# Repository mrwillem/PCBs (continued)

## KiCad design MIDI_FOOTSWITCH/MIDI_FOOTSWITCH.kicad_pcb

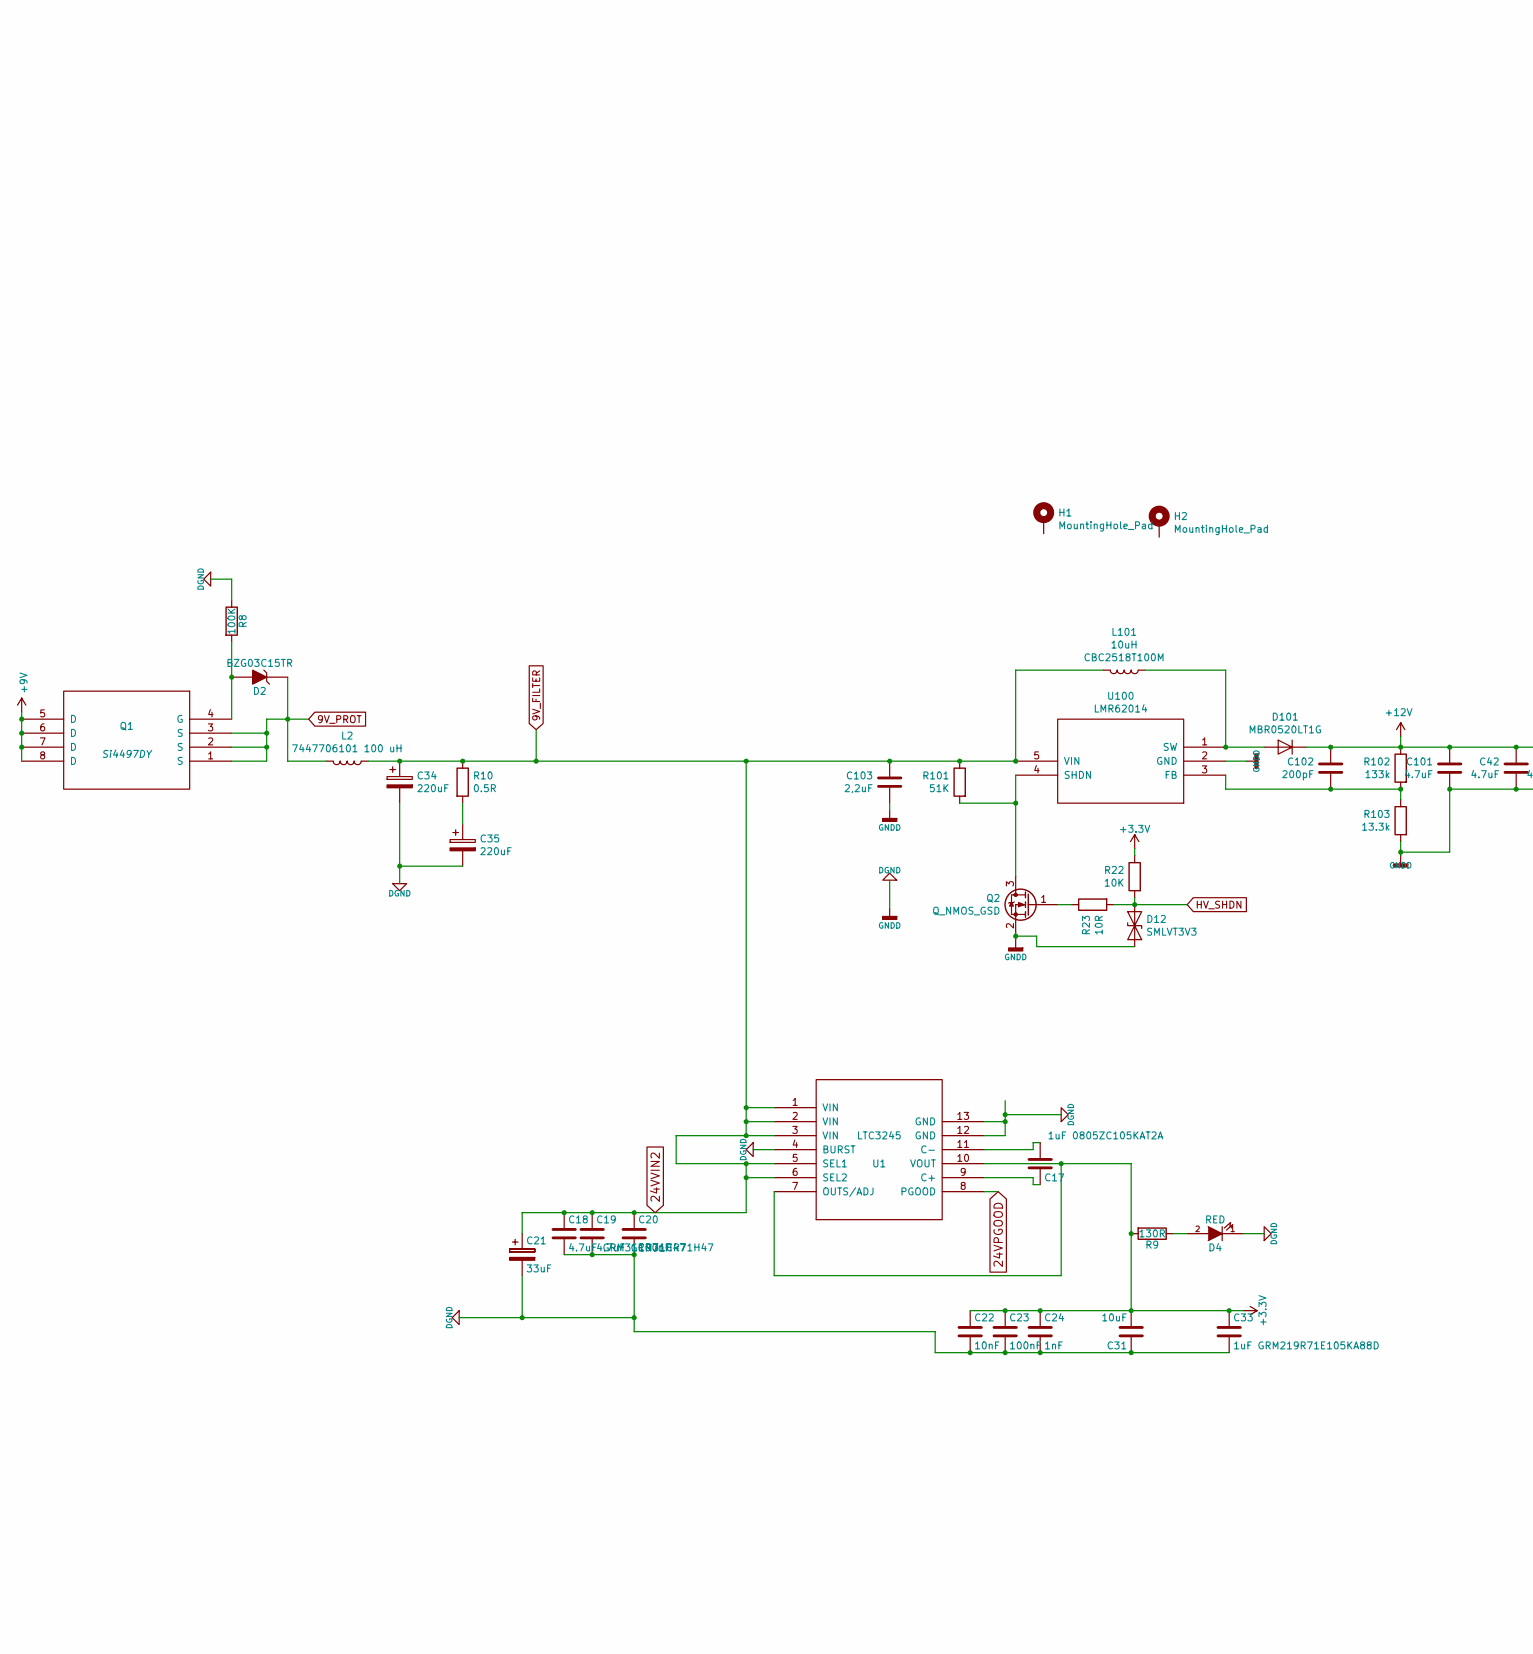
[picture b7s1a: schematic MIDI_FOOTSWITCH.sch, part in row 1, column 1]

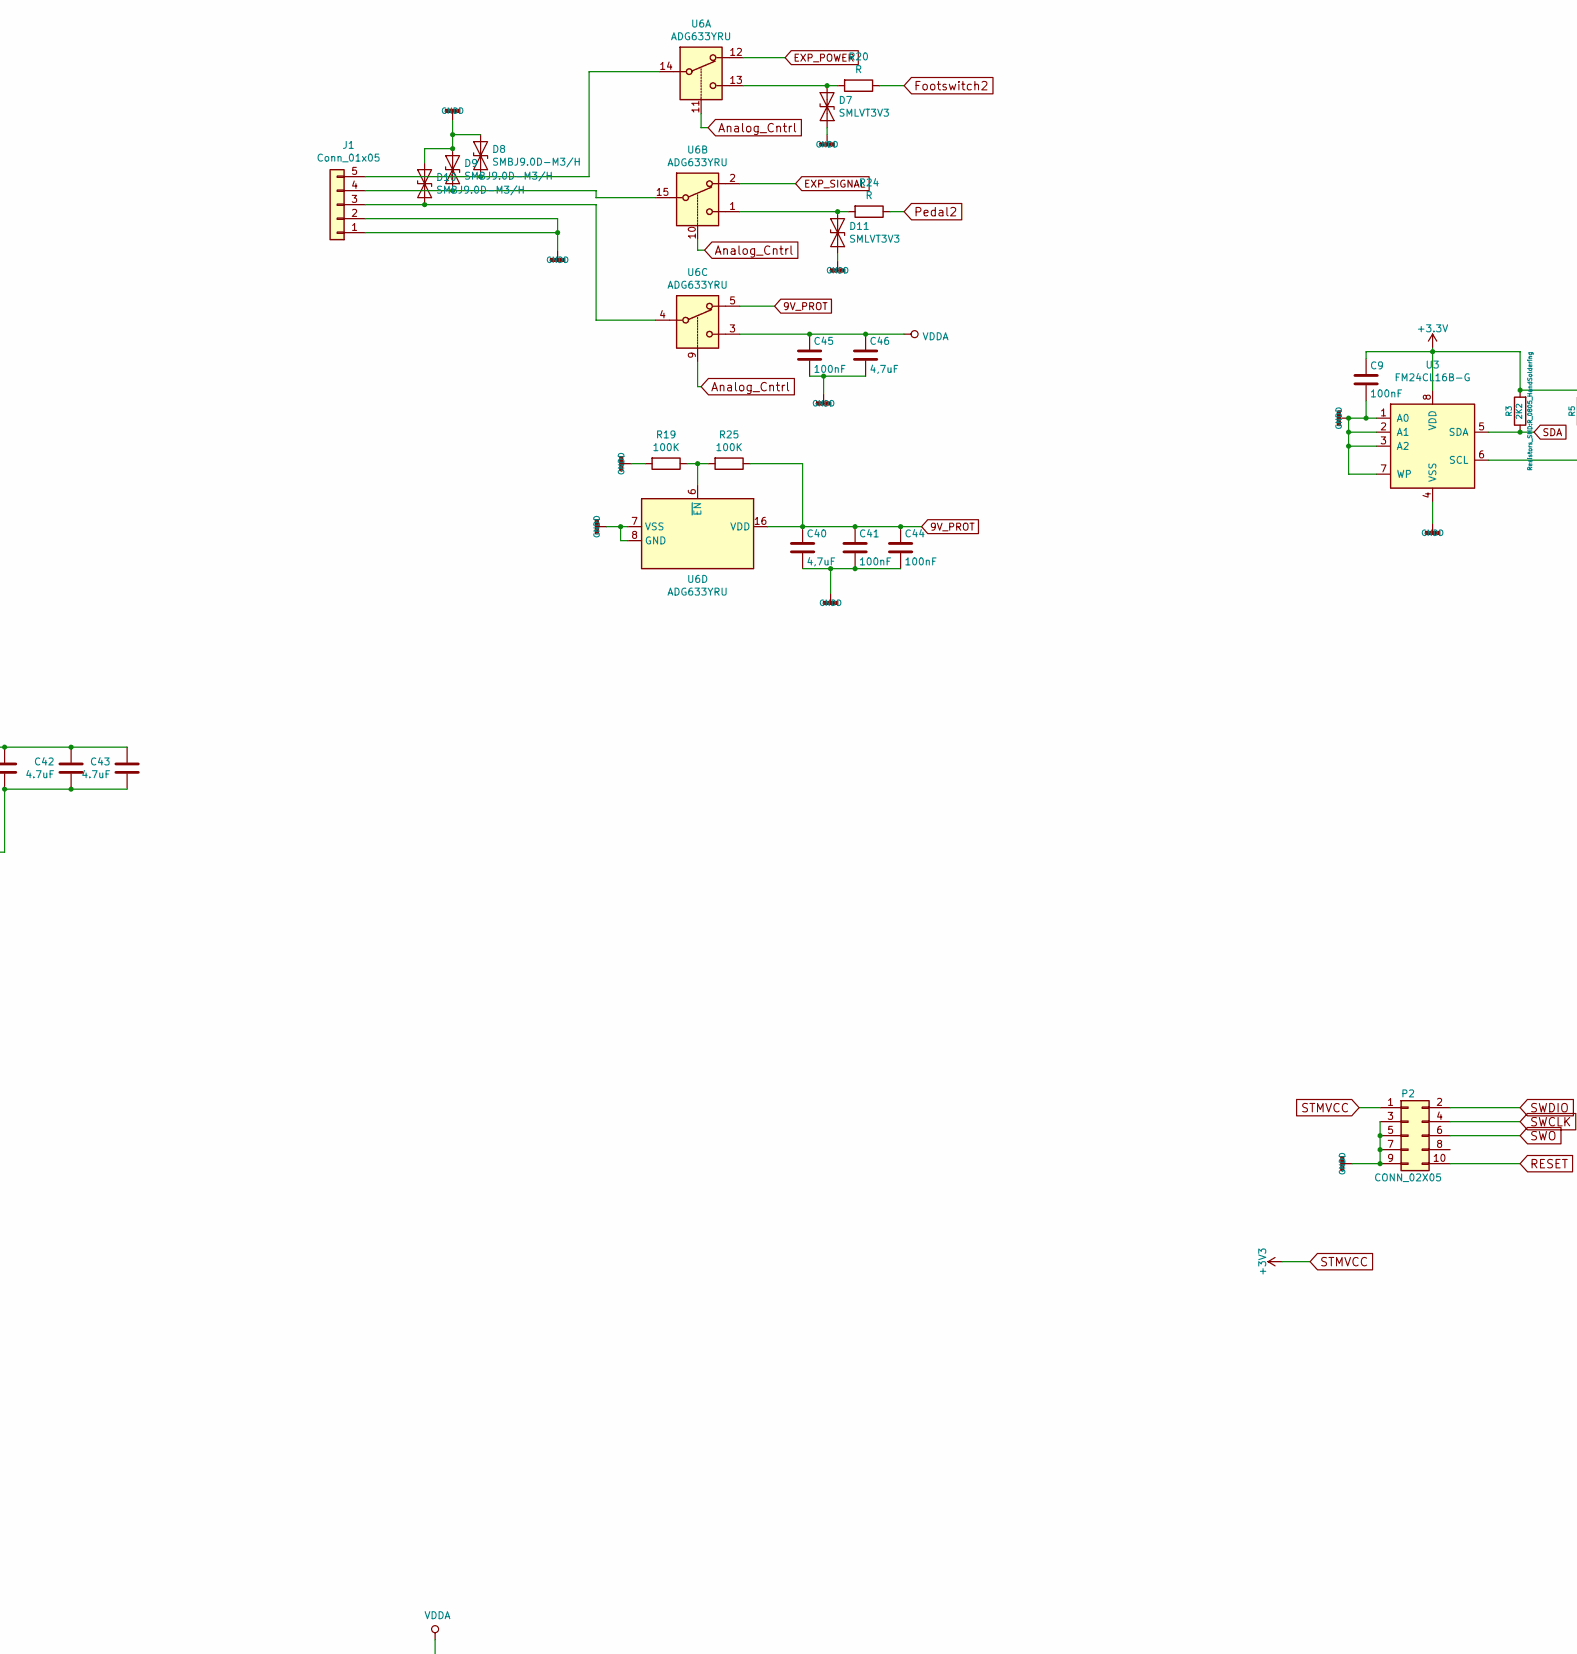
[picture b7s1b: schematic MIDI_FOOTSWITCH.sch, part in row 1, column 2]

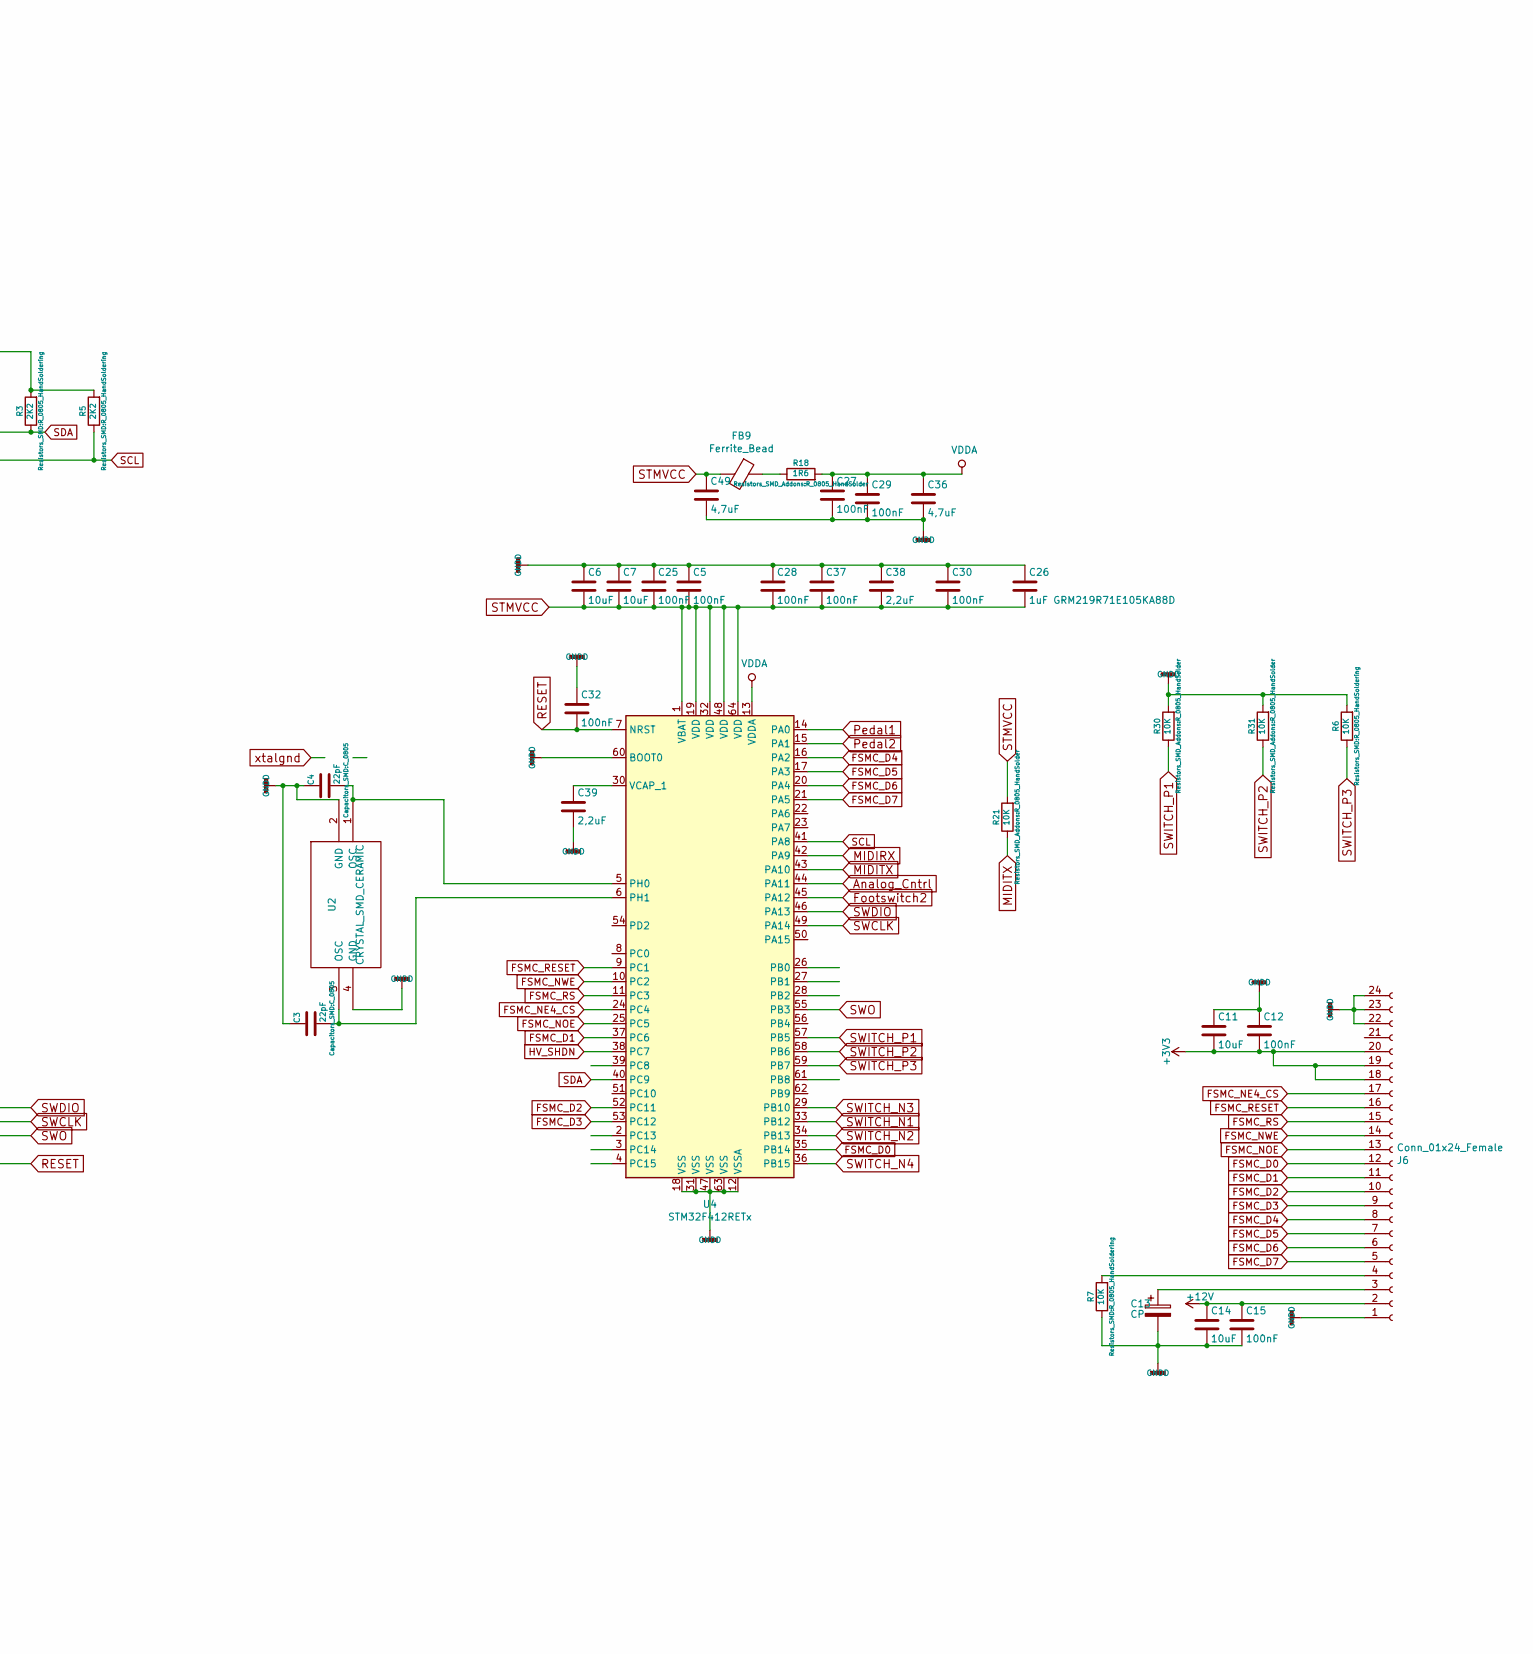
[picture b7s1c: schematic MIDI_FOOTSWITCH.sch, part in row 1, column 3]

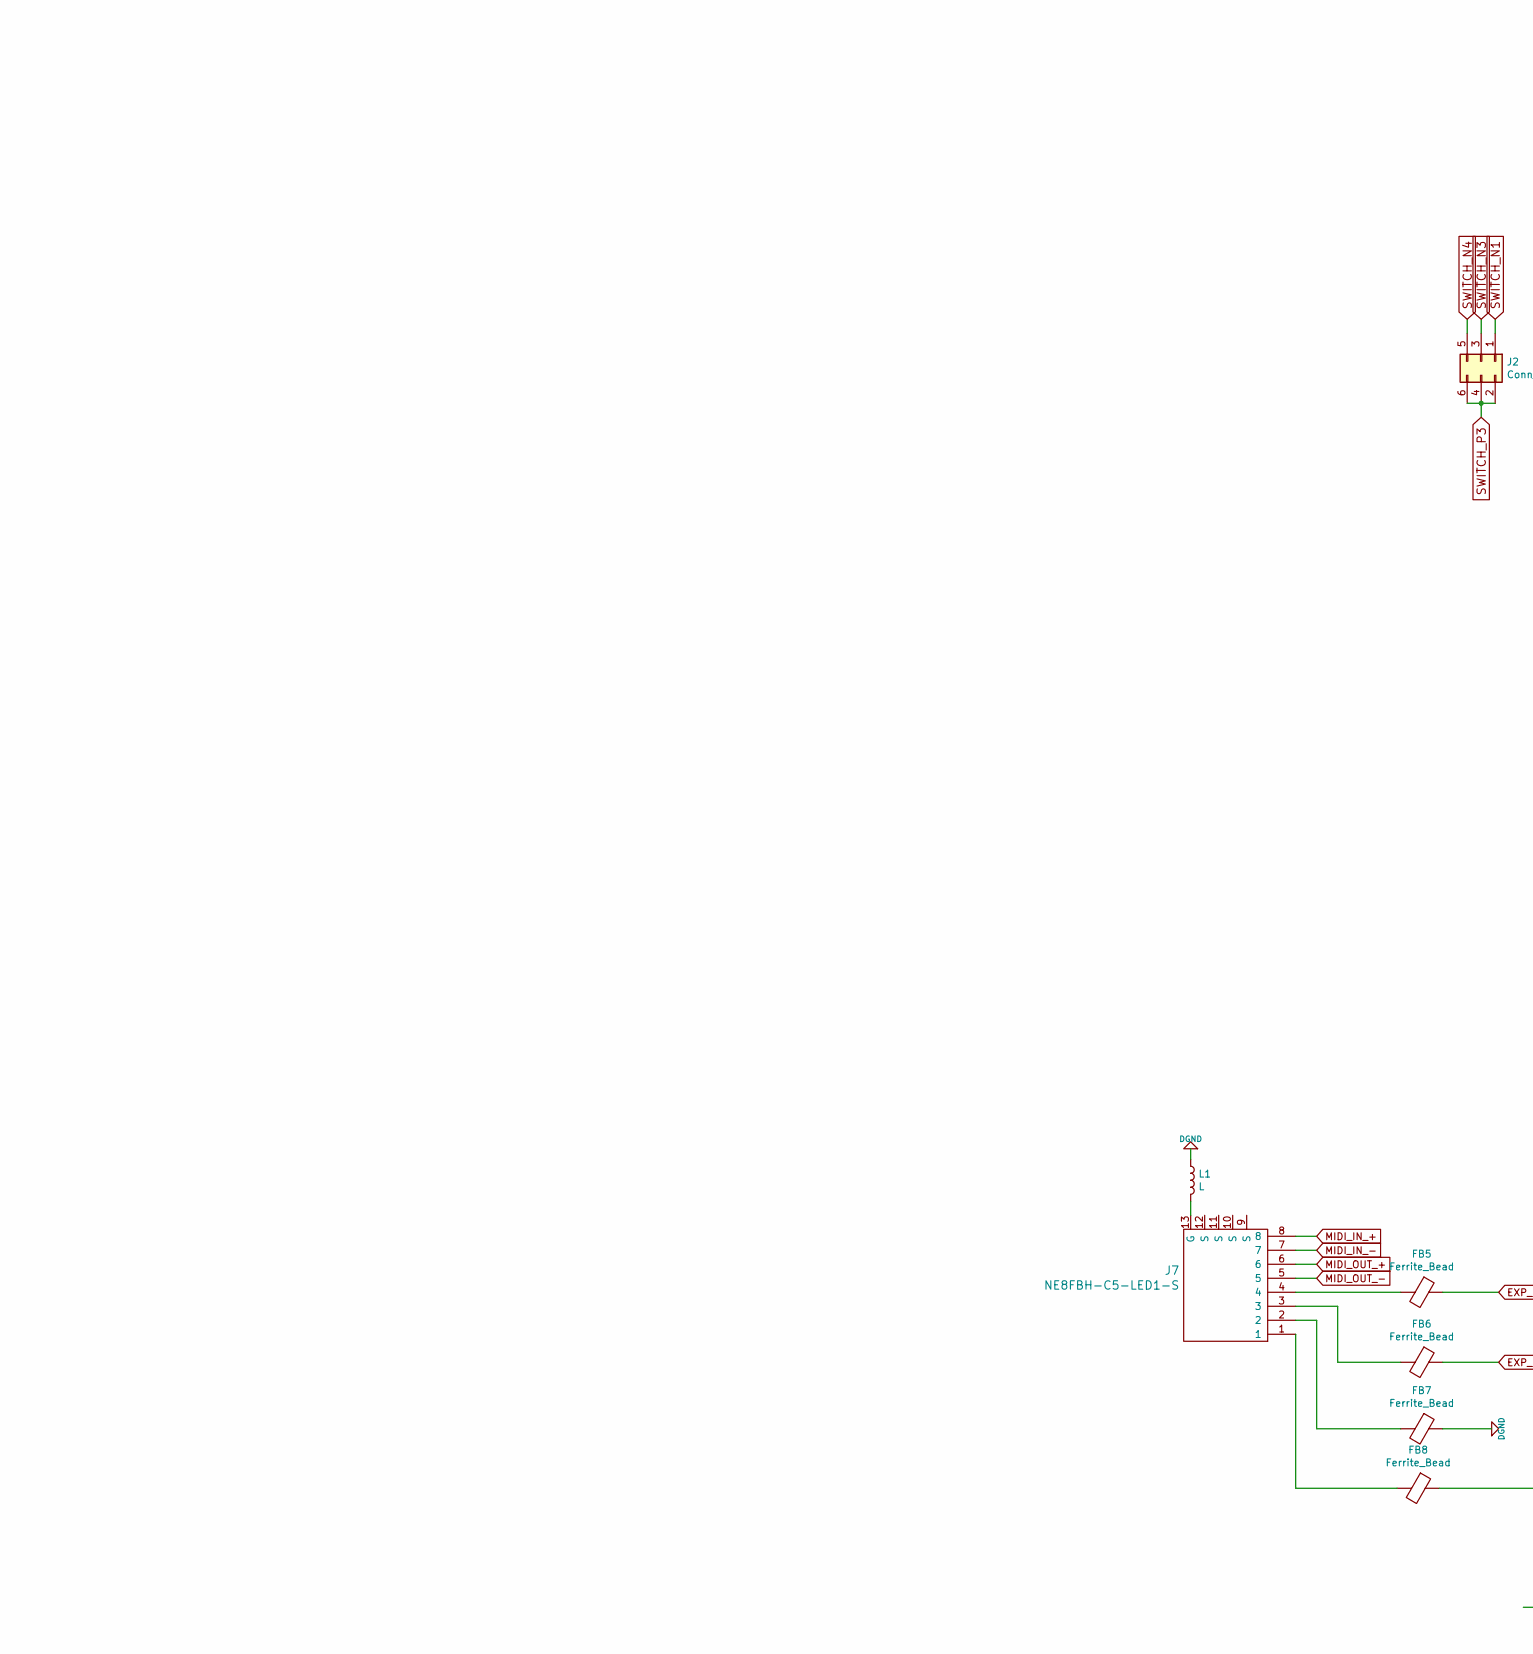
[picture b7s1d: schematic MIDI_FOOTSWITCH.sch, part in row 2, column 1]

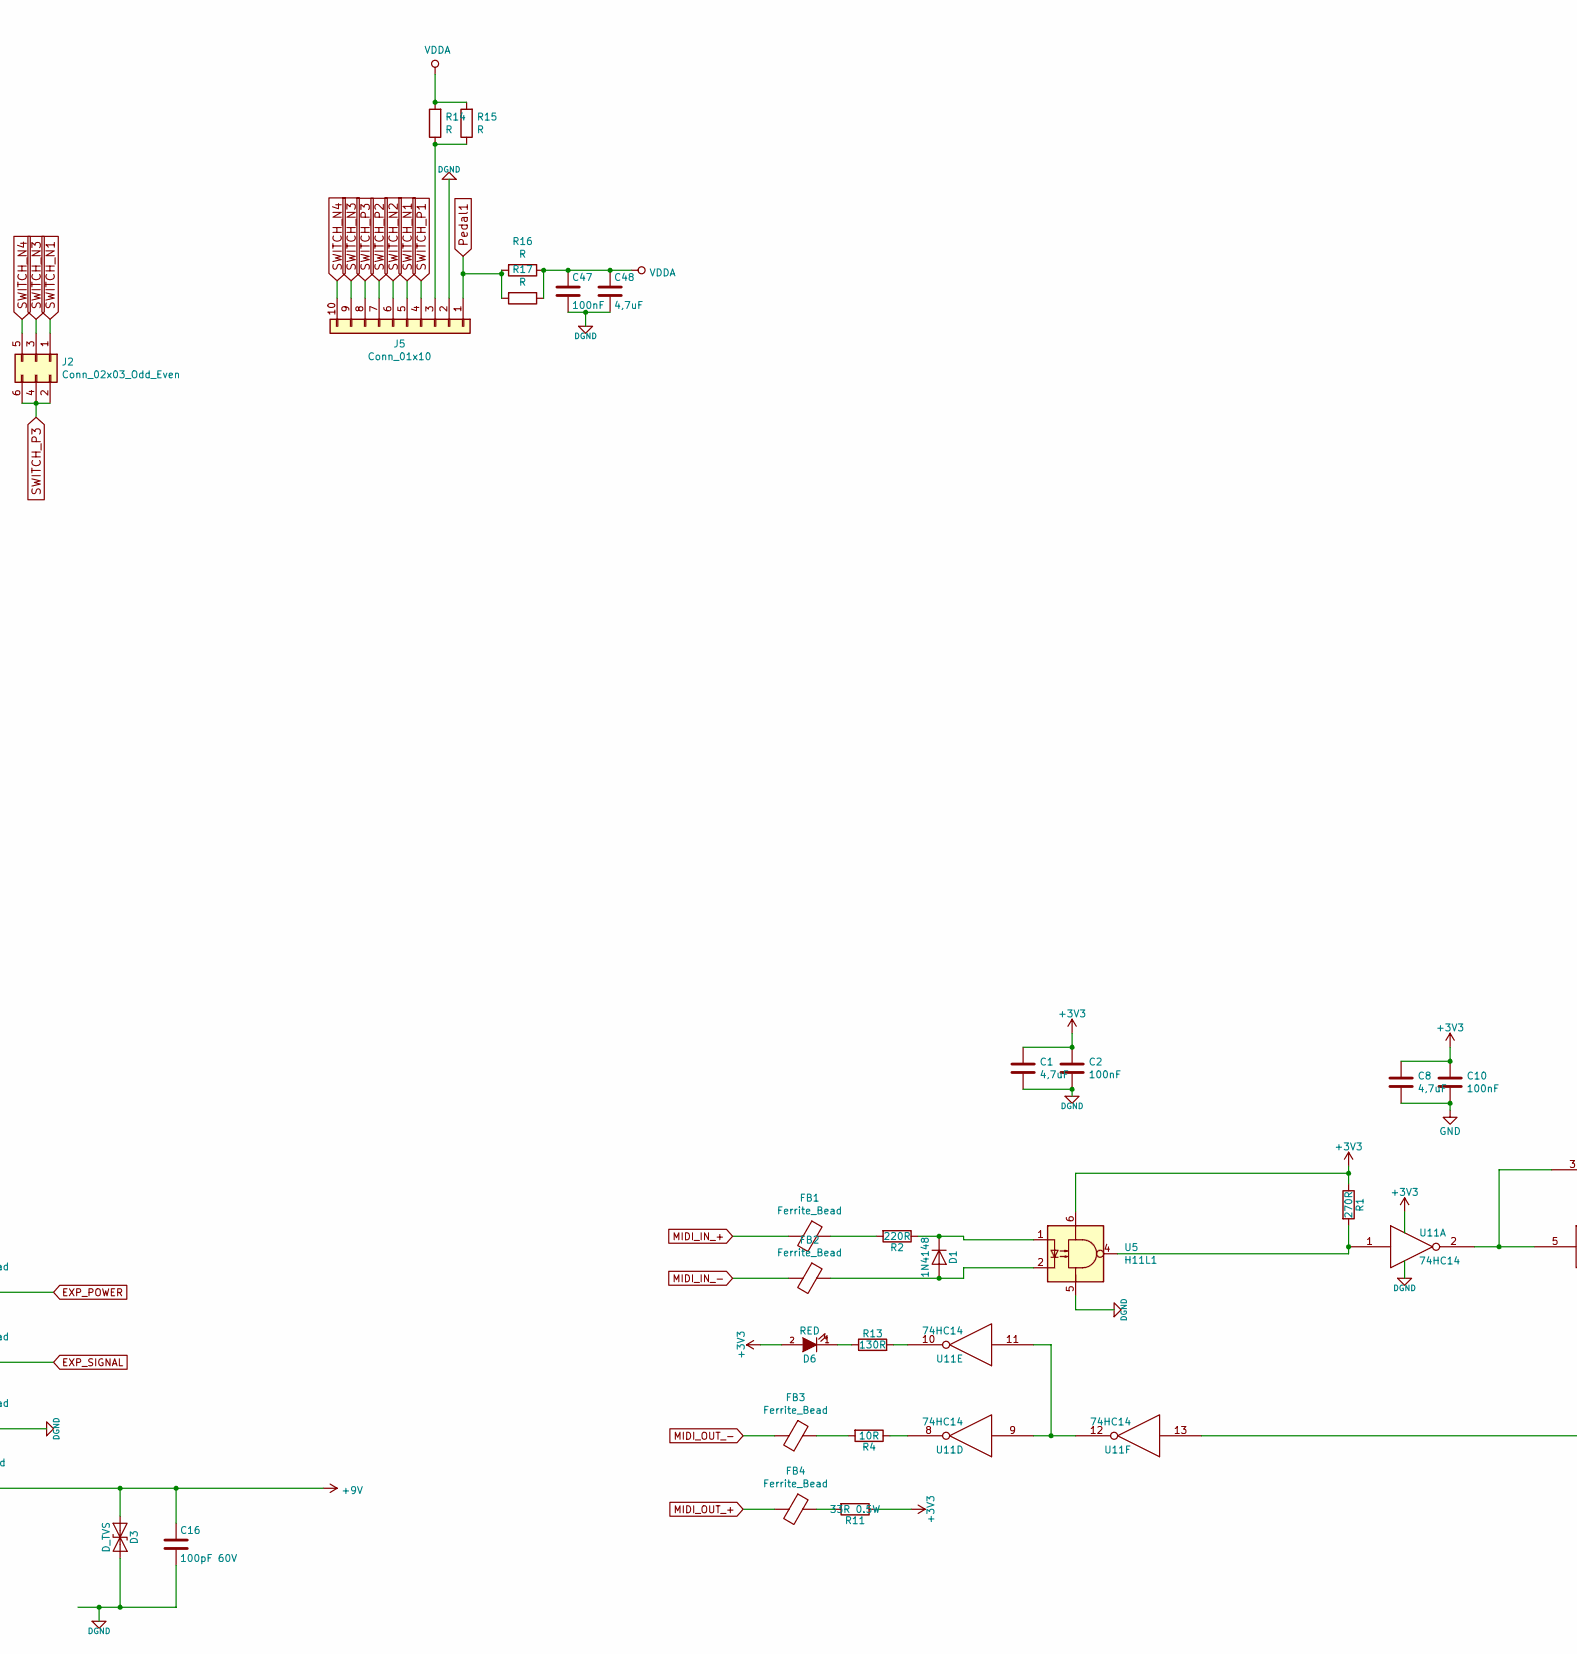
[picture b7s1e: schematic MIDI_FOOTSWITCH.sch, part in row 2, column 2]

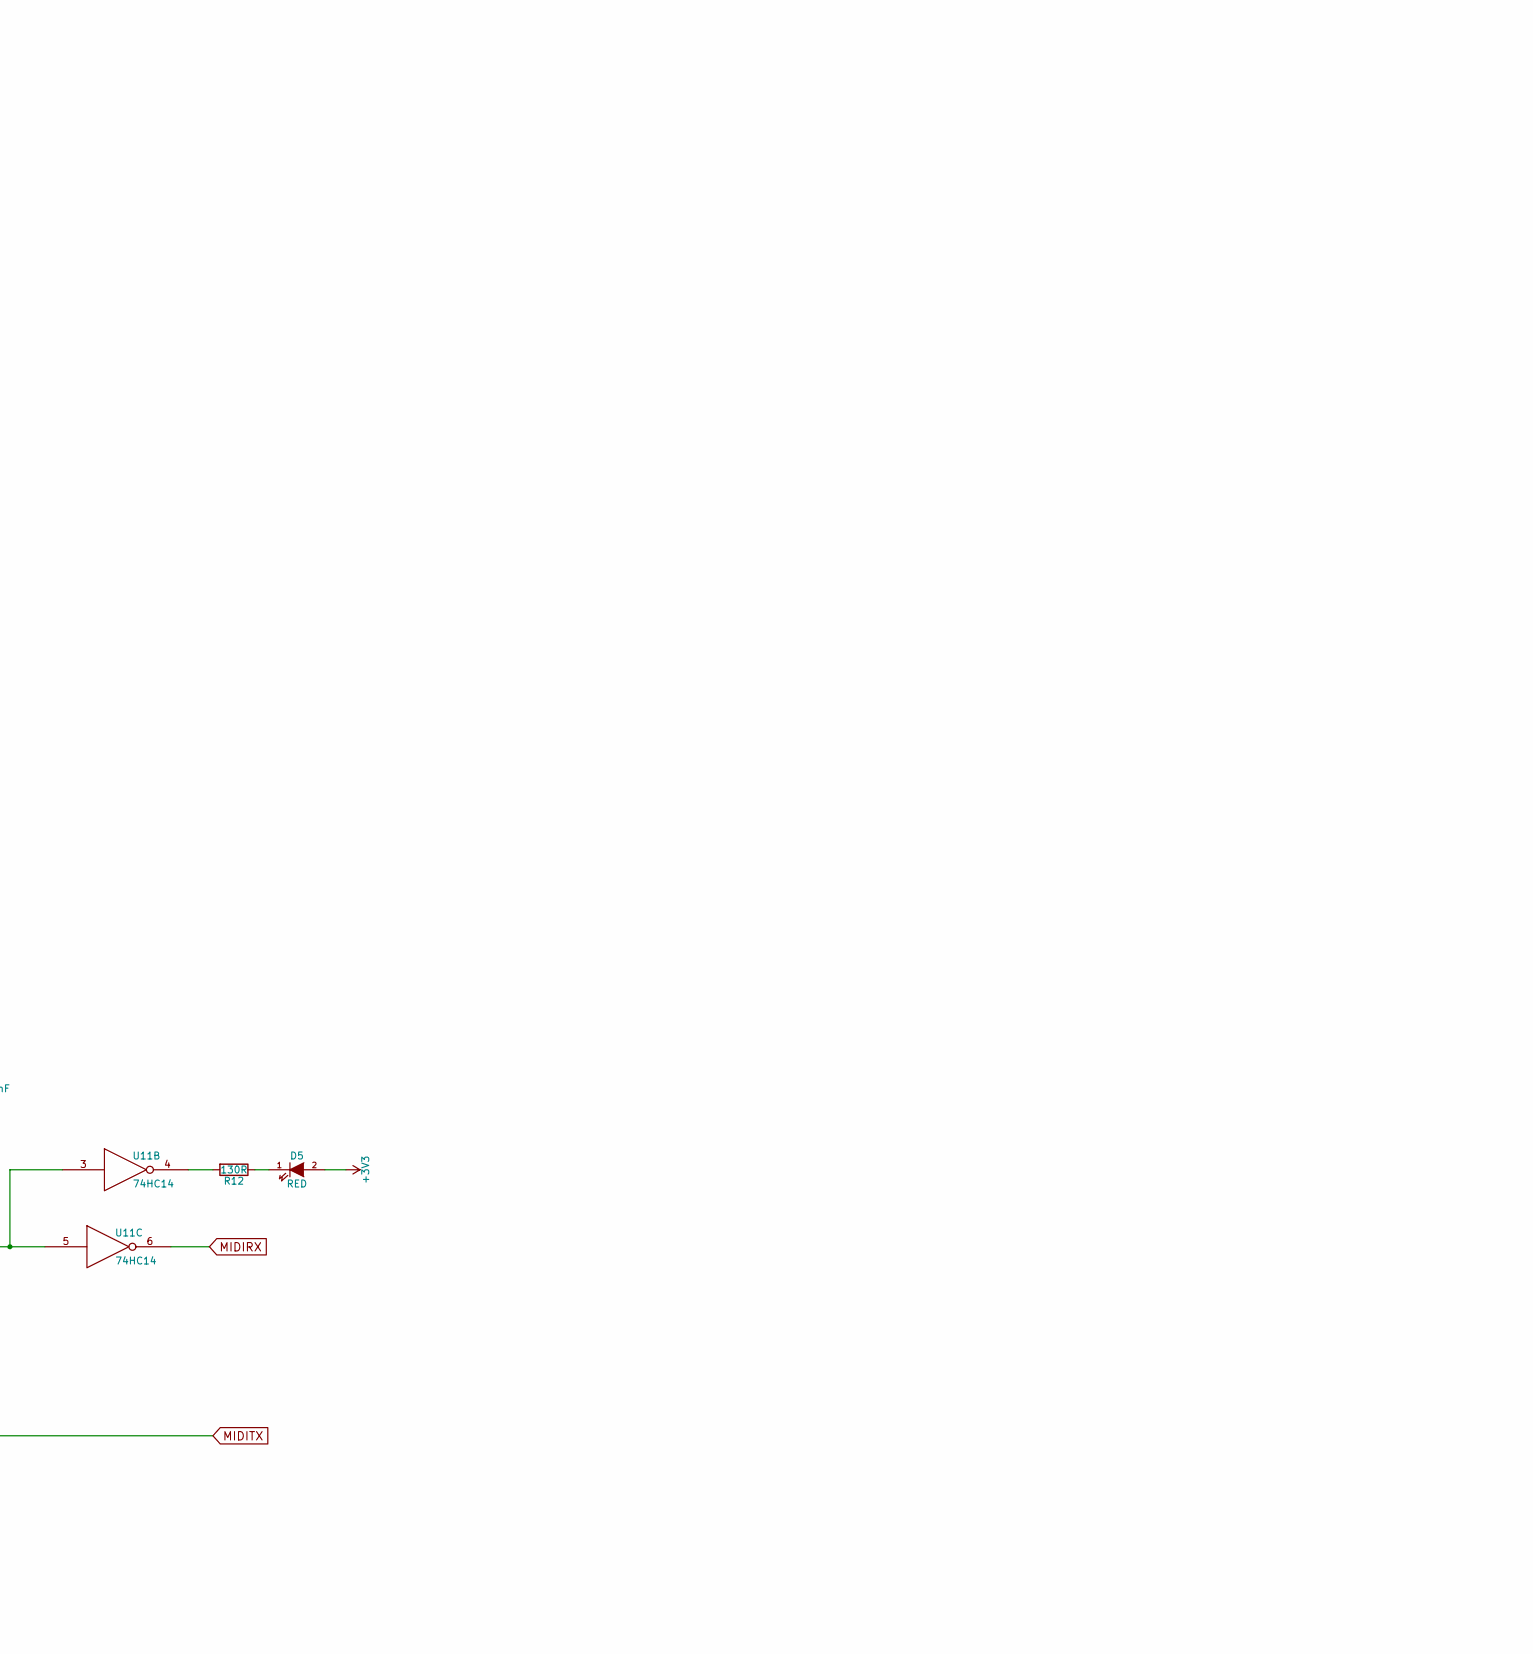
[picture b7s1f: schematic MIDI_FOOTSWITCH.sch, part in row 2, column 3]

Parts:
C1, C8, C36, C40, C46, C48, C49: 4,7uF; R_0805_HandSolder
C2, C5, C9, C10, C12, C15, C20, C23, C25, C27, C28, C29, C30, C32, C37, C41, C44, C45, C47: 100nF; R_0603_HandSolder
C3, C4: 22pF; C_0805
C6, C7, C11, C14: 10uF; R_0805_HandSolder
C13: CP; C_1210
C16: 100pF 60V; C_0805
C17: 1uF 0805ZC105KAT2A; R_0805_HandSolder
C18, C19: 4.7uF GRM31CR71H47; C_1206
C21: 33uF; CP_Elec_6.3x7.7
C22: 10nF; R_0805_HandSolder
C24: 1nF; C_0805
C26, C33: 1uF GRM219R71E105KA88D; C_0805
C31: 10uF; C_0805
C34, C35: 220uF; CP_Elec_10x10.5
C38, C39, C103: 2,2uF; R_0805_HandSolder
C42, C43, C101: 4.7uF; R_0805_HandSolder
C102: 200pF; R_0805_HandSolder
D1: 1N4148; SOD-323-Handsoldering
D2: BZG03C15TR; D_SMA_Handsoldering
D3: D_TVS; D_SMB_Handsoldering
D4, D5, D6: RED; LED_0805_HandSoldering
D7, D11, D12: SMLVT3V3; D_SMA
D8, D9, D10: SMBJ9.0D-M3/H; D_SMA
D101: MBR0520LT1G; D_SOD-110
FB1, FB2, FB3, FB4, FB5, FB6, FB7, FB8, FB9: Ferrite_Bead; R_0805_HandSolder
H1, H2: MountingHole_Pad; MountingHole_3.2mm_M3_Pad
J1: Conn_01x05; Neutrik_NC5FAH
J2: Conn_02x03_Odd_Even; Pin_Header_Straight_2x03_Pitch2.54mm
J5: Conn_01x10; Pin_Header_Straight_1x10_Pitch2.00mm
J6: Conn_01x24_Female; Hirose_FH12-24S-0.5SH_1x24-1MP_P0.50mm_Horizontal
J7: NE8FBH-C5-LED1-S; NE8FBH
L1: L; R_0805_HandSolder
L2: 7447706101 100 uH; Choke_SMD_12x12mm_h8mm
L101: 10uH; Inductor_Taiyo-Yuden_NR-40xx_HandSoldering
P2: CONN_02X05; Pin_Header_Straight_2x05_Pitch1.27mm
Q1: Si4497DY; SO-8_5.3x6.2mm_Pitch1.27mm
Q2: Q_NMOS_GSD; SOT-723
R1: 270R; R_0805_HandSolder
R2: 220R; R_0805_HandSolder
R3, R5: 2K2; R_0805_HandSoldering
R4, R23: 10R; R_0805_HandSolder
R6, R7: 10K; R_0805_HandSoldering
R8: 100K; R_0603_HandSolder
R9, R12, R13: 130R; R_0805_HandSolder
R10: 0.5R; R_0805_HandSolder
R11: 33R 0.5W; R_0805_HandSolder
R14, R15, R16, R17, R20, R24: R; R_0805_HandSolder
R18: 1R6; R_0805_HandSolder
R19, R25: 100K; R_0805_HandSolder
R21, R22, R30, R31: 10K; R_0805_HandSolder
R101: 51K; R_0805_HandSolder
R102: 133k; R_0805_HandSolder
R103: 13.3k; R_0805_HandSolder
U1: LTC3245; MSOP-12-1EP_3x4mm_Pitch0.65mm
U2: CRYSTAL_SMD_CERAMIC; Xtal_Ceramic_5x3.2
U3: FM24CL16B-G; SOIC-8_3.9x4.9mm_Pitch1.27mm
U4: STM32F412RETx; LQFP-64_10x10mm_Pitch0.5mm
U5: H11L1; SO6_DIL_GULLWING
U6: ADG633YRU; TSSOP-16_4.4x5mm_Pitch0.65mm
U11: 74HC14; SOIC-14_3.9x8.7mm_Pitch1.27mm
U100: LMR62014; SOT-23-5_HandSoldering

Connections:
9V_PROT: C40.1, C41.1, C44.1, D2.1 (K), L2.2, Q1.1 (S), Q1.2 (S), Q1.3 (S), R25.1, U6.5, U6.16 (VDD)
24VVIN2: C18.1, C19.1, C20.1, C21.1, C34.1, C103.1, L2.1, L101.1, R10.1, R101.1, U1.1 (VIN), U1.2 (VIN), U1.3 (VIN), U1.5 (SEL1), U1.6 (SEL2), U100.5 (VIN)
+9V: C16.1, D3.1 (A1), FB8.1, Q1.5 (D), Q1.6 (D), Q1.7 (D), Q1.8 (D)
+12V: C14.1, C15.1, C42.1, C43.1, C101.1, C102.1, D101.1 (K), J6.2, R102.1
Analog_Cntrl: U4.44 (PA11), U6.9, U6.10, U6.11
EXP_POWER: FB5.1, U6.12
EXP_SIGNAL: FB6.1, U6.2
FSMC_D0: J6.12, U4.35 (PB14)
FSMC_D1: J6.11, U4.37 (PC6)
FSMC_D2: J6.10, U4.52 (PC11)
FSMC_D3: J6.9, U4.53 (PC12)
FSMC_D4: J6.8, U4.16 (PA2)
FSMC_D5: J6.7, U4.17 (PA3)
FSMC_D6: J6.6, U4.20 (PA4)
FSMC_D7: J6.5, U4.21 (PA5)
FSMC_NE4_CS: J6.17, U4.24 (PC4)
FSMC_NOE: J6.13, U4.25 (PC5)
FSMC_NWE: J6.14, U4.10 (PC2)
FSMC_RESET: J6.16, U4.9 (PC1)
FSMC_RS: J6.15, U4.11 (PC3)
Footswitch2: R20.1, U4.45 (PA12)
HV_SHDN: D12.1 (A1), R22.2, R23.2, U4.38 (PC7)
MIDIRX: U4.42 (PA9), U11.6
MIDITX: R21.1, U4.43 (PA10), U11.13
MIDI_IN_+: FB1.2, J7.8
MIDI_IN_-: FB2.2, J7.7
MIDI_OUT_+: FB4.2, J7.6
MIDI_OUT_-: FB3.2, J7.5
unnamed: C3.2, U2.3 (OSC), U4.6 (PH1)
unnamed: C4.2, U2.1 (OSC), U4.5 (PH0)
unnamed: C13.1, J6.3
unnamed: C17.1, U1.9 (C+)
unnamed: C17.2, U1.11 (C-)
unnamed: C35.1, R10.2
unnamed: C39.1, U4.30 (VCAP_1)
unnamed: C102.2, R102.2, R103.1, U100.3 (FB)
unnamed: D1.1 (K), R2.1, U5.1
unnamed: D1.2 (A), FB2.1, U5.2
unnamed: D2.2 (A), Q1.4 (G), R8.2
unnamed: D4.2 (A), R9.1
unnamed: D5.1 (K), R12.1
unnamed: D6.1 (K), R13.1
unnamed: D7.1 (A1), R20.2, U6.13
unnamed: D8.2 (A2), J1.5, U6.14
unnamed: D9.2 (A2), J1.4, U6.15
unnamed: D10.2 (A2), J1.3, U6.4
unnamed: D11.1 (A1), R24.2, U6.1
unnamed: D101.2 (A), L101.2, U100.1 (SW)
unnamed: FB1.1, R2.2
unnamed: FB3.1, R4.2
unnamed: FB4.1, R11.2
unnamed: FB5.2, J7.4
unnamed: FB6.2, J7.3
unnamed: FB7.2, J7.2
unnamed: FB8.2, J7.1
unnamed: FB9.1, R18.1
unnamed: J5.3, R14.1, R15.1
unnamed: J6.4, R7.2
unnamed: J7.13 (G), L1.2
unnamed: Q2.1 (G), R23.1
unnamed: Q2.3 (D), R101.2, U100.4 (SHDN)
unnamed: R1.2, U5.4, U11.1
unnamed: R4.1, U11.8
unnamed: R12.2, U11.4
unnamed: R13.2, U11.10
unnamed: R19.1, R25.2, U6.6 (~EN)
unnamed: U11.2, U11.3, U11.5
unnamed: U11.9, U11.11, U11.12
Pedal1: J5.1, R16.2, R17.2, U4.14 (PA0)
Pedal2: R24.1, U4.15 (PA1)
RESET: C32.2, P2.10, U4.7 (NRST)
SCL: R5.1, U3.6 (SCL), U4.41 (PA8)
SDA: R3.1, U3.5 (SDA), U4.40 (PC9)
SWCLK: P2.4, U4.49 (PA14)
SWDIO: P2.2, U4.46 (PA13)
SWITCH_N1: J2.1, J5.5, U4.33 (PB12)
SWITCH_N2: J5.6, U4.34 (PB13)
SWITCH_N3: J2.3, J5.9, U4.29 (PB10)
SWITCH_N4: J2.5, J5.10, U4.36 (PB15)
SWITCH_P1: J5.4, R30.1, U4.57 (PB5)
SWITCH_P2: J5.7, R31.1, U4.58 (PB6)
SWITCH_P3: J2.2, J2.4, J2.6, J5.8, R6.1, U4.59 (PB7)
SWO: P2.6, U4.55 (PB3)
VDDA: C27.1, C29.1, C36.1, C45.1, C46.1, C47.1, C48.1, R14.2, R15.2, R16.1, R17.1, R18.2, U4.13 (VDDA), U6.3

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
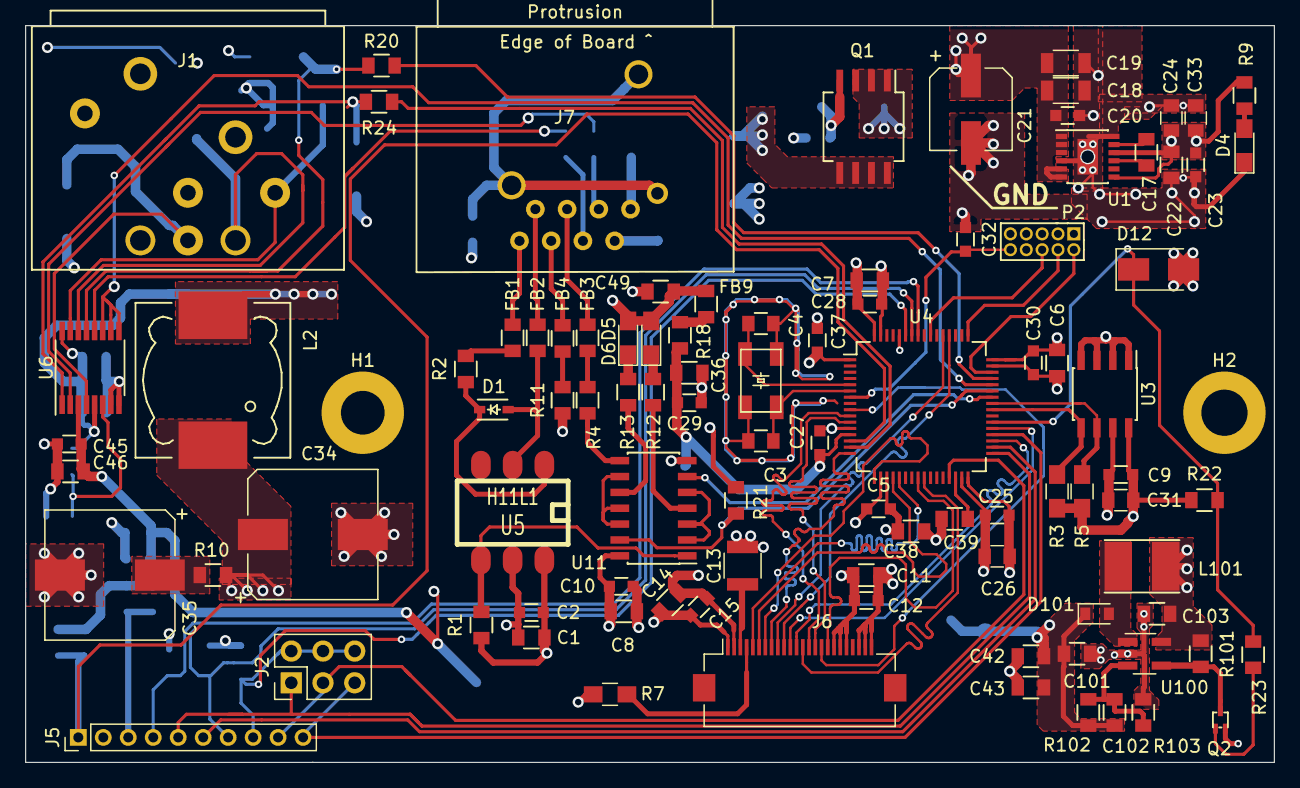
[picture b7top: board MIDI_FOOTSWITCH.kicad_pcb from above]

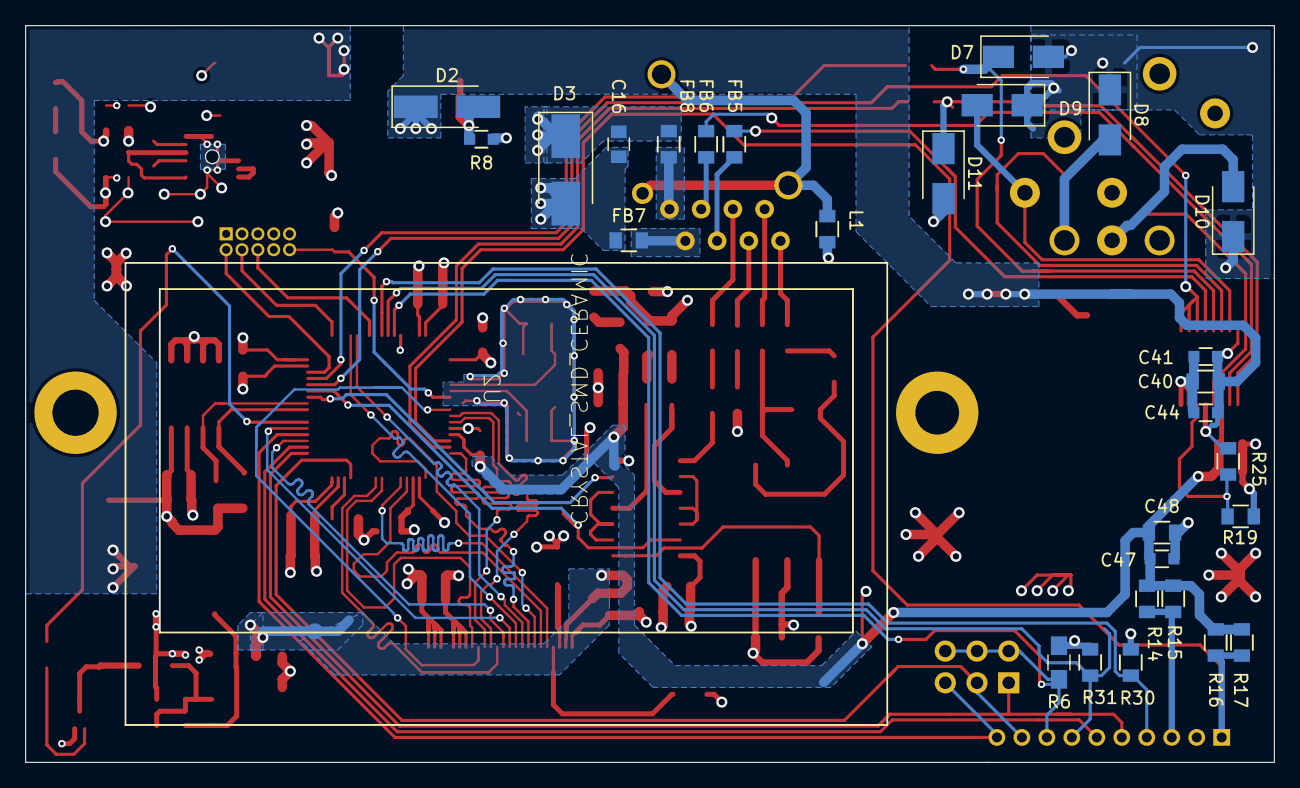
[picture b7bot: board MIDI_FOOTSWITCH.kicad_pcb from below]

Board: 4 copper layers, 100.0 x 59.0 mm, 125 parts (28 on the bottom side), 86 nets.
